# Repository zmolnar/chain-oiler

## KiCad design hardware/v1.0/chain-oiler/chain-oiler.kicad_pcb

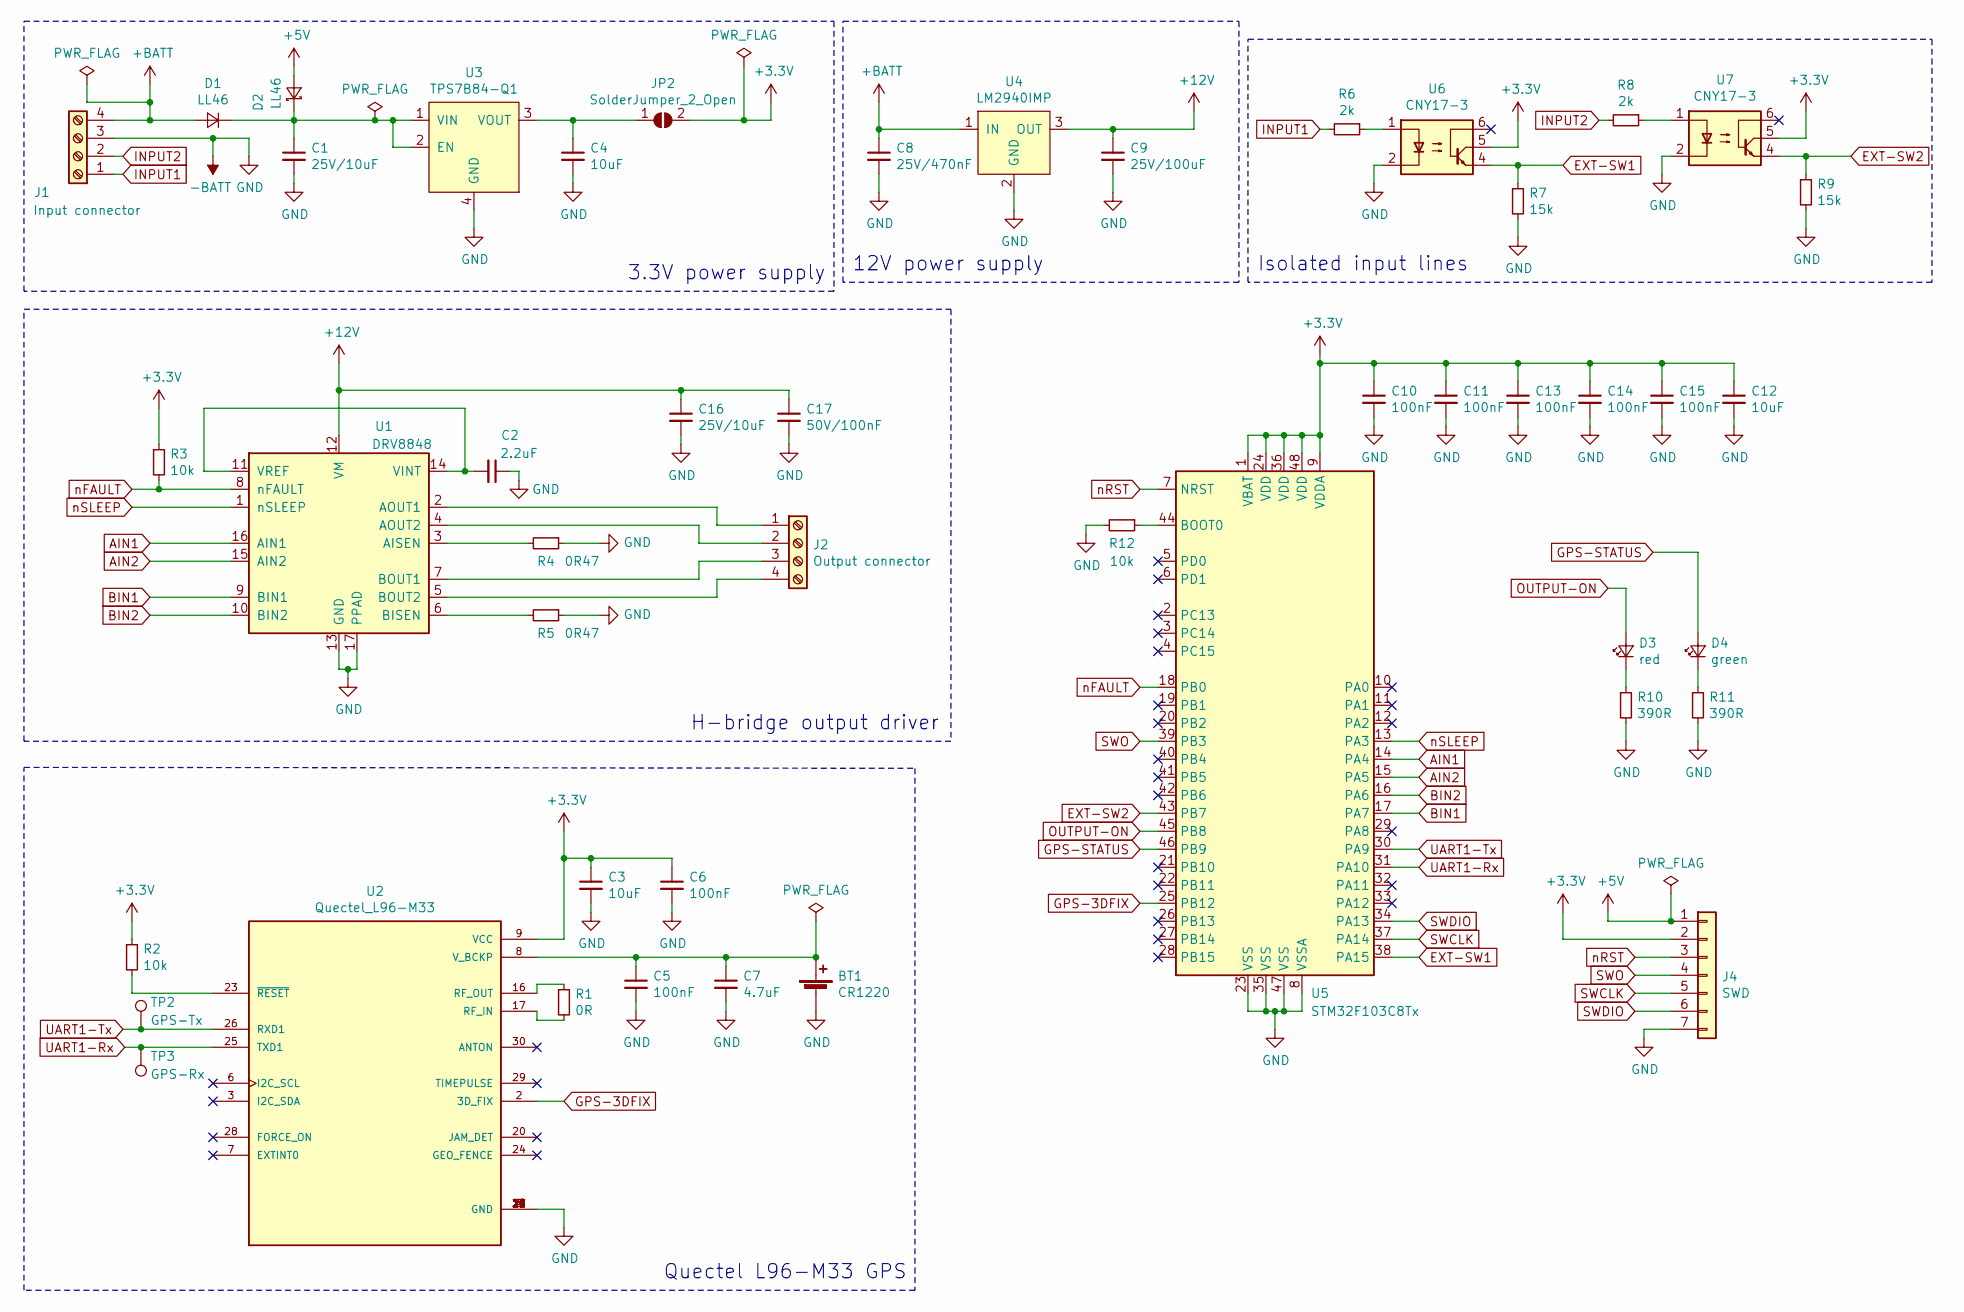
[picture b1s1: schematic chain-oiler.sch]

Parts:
BT1: CR1220; BatteryHolder_Keystone_3001_1x12mm
C1, C16: 25V/10uF; C_0805_2012Metric_Pad1.15x1.40mm_HandSolder
C2: 2.2uF; C_0805_2012Metric_Pad1.15x1.40mm_HandSolder
C3, C4, C12: 10uF; C_0603_1608Metric_Pad1.05x0.95mm_HandSolder
C5, C6, C10, C11, C13, C14, C15: 100nF; C_0603_1608Metric_Pad1.05x0.95mm_HandSolder
C7: 4.7uF; C_0603_1608Metric_Pad1.05x0.95mm_HandSolder
C8: 25V/470nF; C_0603_1608Metric_Pad1.05x0.95mm_HandSolder
C9: 25V/100uF; CP_Radial_D6.3mm_P2.50mm
C17: 50V/100nF; C_0603_1608Metric_Pad1.05x0.95mm_HandSolder
D1, D2: LL46; D_MiniMELF
D3: red; D_0603_1608Metric_Pad1.05x0.95mm_HandSolder
D4: green; D_0603_1608Metric_Pad1.05x0.95mm_HandSolder
J1: Input connector; Tianli_TLPHC100R_3.81_01x04
J2: Output connector; Tianli_TLPHC100R_3.81_01x04
J4: SWD; PinHeader_1x07_P2.54mm_Vertical
JP2: SolderJumper_2_Open; SolderJumper-2_P1.3mm_Open_TrianglePad1.0x1.5mm
R1: 0R; R_0603_1608Metric_Pad1.05x0.95mm_HandSolder
R2, R3, R12: 10k; R_0603_1608Metric_Pad1.05x0.95mm_HandSolder
R4, R5: 0R47; R_0805_2012Metric_Pad1.15x1.40mm_HandSolder
R6, R8: 2k; R_0603_1608Metric_Pad1.05x0.95mm_HandSolder
R7, R9: 15k; R_0805_2012Metric_Pad1.15x1.40mm_HandSolder
R10, R11: 390R; R_0603_1608Metric_Pad1.05x0.95mm_HandSolder
TP2: GPS-Tx; TestPoint_Pad_D1.0mm
TP3: GPS-Rx; TestPoint_Pad_D1.0mm
U1: DRV8848; TSSOP-16-1EP_4.4x5mm_P0.65mm
U2: Quectel_L96-M33
U3: TPS7B84-Q1; SOT-223
U4: LM2940IMP; SOT-223-3_TabPin2
U5: STM32F103C8Tx; LQFP-48_7x7mm_P0.5mm
U6, U7: CNY17-3; SMDIP-6_W9.53mm

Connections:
+3V3: C3.1, C6.1, C10.1, C11.1, C12.1, C13.1, C14.1, C15.1, J4.2, JP2.2 (B), R2.1, R3.1, U2.9 (VCC), U5.1 (VBAT), U5.9 (VDDA), U5.24 (VDD), U5.36 (VDD), U5.48 (VDD), U6.5, U7.5
+5V: D2.2 (A), J4.1
+12V: C9.1, C16.1, C17.1, U1.12 (VM), U4.3 (OUT)
+BATT: C8.1, D1.2 (A), J1.4, U4.1 (IN)
-BATT: BT1.2 (-), C1.2, C2.1, C3.2, C4.2, C5.2, C6.2, C7.2, C8.2, C9.2, C10.2, C11.2, C12.2, C13.2, C14.2, C15.2, C16.2, C17.2, J1.3, J4.7, R4.1, R5.1, R7.2, R9.2, R10.2, R11.2, R12.2, U1.13 (GND), U1.17 (PPAD), U2.4 (GND), U2.5 (GND), U2.10 (GND), U2.11 (GND), U2.12 (GND), U2.13 (GND), U2.14 (GND), U2.15 (GND), U2.18 (GND), U2.19 (GND), U2.21 (GND), U2.22 (GND), U2.27 (GND), U2.31 (GND), U3.4 (GND), U4.2 (GND), U5.8 (VSSA), U5.23 (VSS), U5.35 (VSS), U5.47 (VSS), U6.2, U7.2
AIN1: U1.16 (AIN1), U5.14 (PA4)
AIN2: U1.15 (AIN2), U5.15 (PA5)
BIN1: U1.9 (BIN1), U5.17 (PA7)
BIN2: U1.10 (BIN2), U5.16 (PA6)
EXT-SW1: R7.1, U5.38 (PA15), U6.4
EXT-SW2: R9.1, U5.43 (PB7), U7.4
GPS-3DFIX: U2.2 (3D_FIX), U5.25 (PB12)
GPS-STATUS: D4.2 (A), U5.46 (PB9)
INPUT1: J1.1, R6.2
INPUT2: J1.2, R8.2
unnamed: BT1.1 (+), C5.1, C7.1, U2.8 (V_BCKP)
unnamed: C1.1, D1.1 (K), D2.1 (K), U3.1 (VIN), U3.2 (EN)
unnamed: C2.2, U1.11 (VREF), U1.14 (VINT)
unnamed: C4.1, JP2.1 (A), U3.3 (VOUT)
unnamed: D3.1 (K), R10.1
unnamed: D4.1 (K), R11.1
unnamed: J2.1, U1.2 (AOUT1)
unnamed: J2.2, U1.4 (AOUT2)
unnamed: J2.3, U1.7 (BOUT1)
unnamed: J2.4, U1.5 (BOUT2)
unnamed: R1.1, U2.16 (RF_OUT)
unnamed: R1.2, U2.17 (RF_IN)
unnamed: R2.2, U2.23 (~RESET)
unnamed: R4.2, U1.3 (AISEN)
unnamed: R5.2, U1.6 (BISEN)
unnamed: R6.1, U6.1
unnamed: R8.1, U7.1
unnamed: R12.1, U5.44 (BOOT0)
OUTPUT-ON: D3.2 (A), U5.45 (PB8)
SWCLK: J4.5, U5.37 (PA14)
SWDIO: J4.6, U5.34 (PA13)
SWO: J4.4, U5.39 (PB3)
UART1-Rx: TP3.1, U2.25 (TXD1), U5.31 (PA10)
UART1-Tx: TP2.1, U2.26 (RXD1), U5.30 (PA9)
nFAULT: R3.2, U1.8 (nFAULT), U5.18 (PB0)
nRST: J4.3, U5.7 (NRST)
nSLEEP: U1.1 (nSLEEP), U5.13 (PA3)

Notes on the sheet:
3.3V power supply
12V power supply
H-bridge output driver
Isolated input lines
Quectel L96-M33 GPS

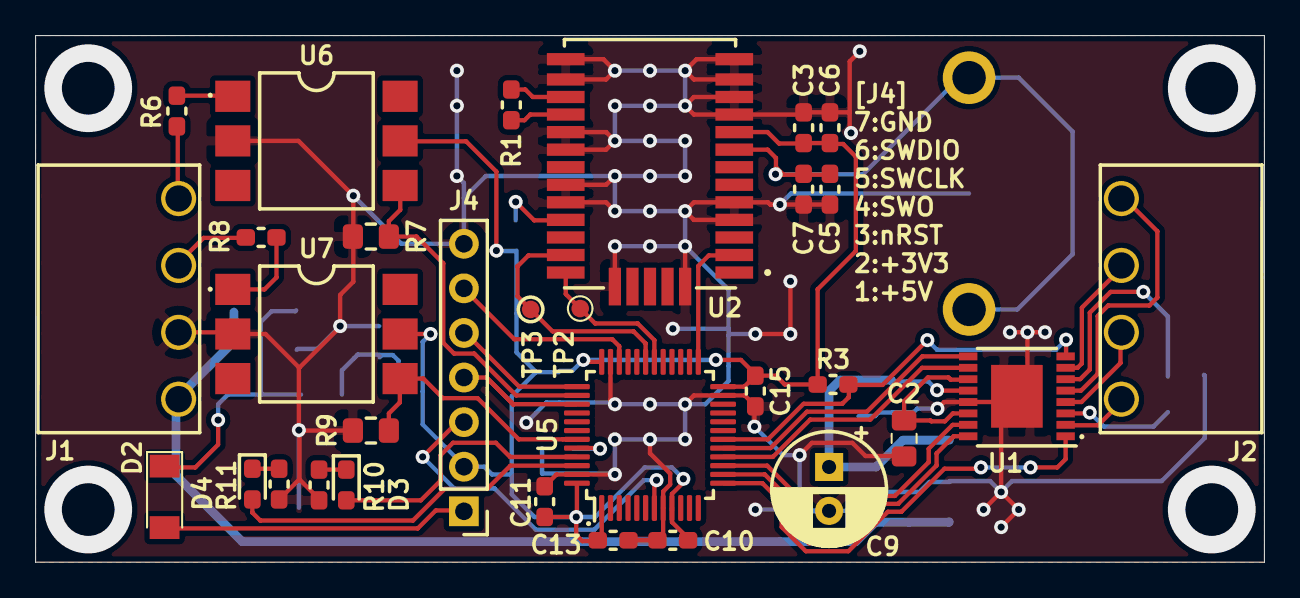
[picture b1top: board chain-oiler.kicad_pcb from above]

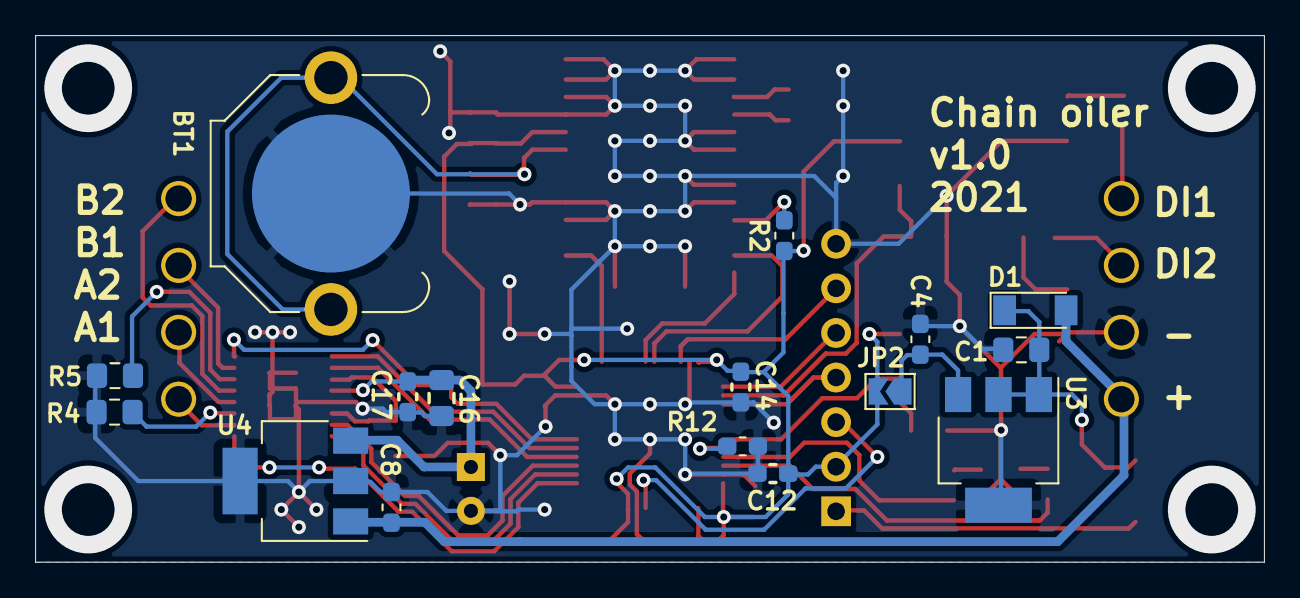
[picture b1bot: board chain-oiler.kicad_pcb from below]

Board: 2 copper layers, 70.0 x 30.0 mm, 47 parts (16 on the bottom side), 42 nets.

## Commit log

2021-07-03 Add v1.0 board project
2021-07-03 Initialize zephyr project
2021-07-20 Add v1.0 hardware design files.
2021-07-20 Add ChibiOS submodule
2021-07-21 Create blinky app
2021-07-21 Add VSCode cortex debug config
2021-07-21 Add GPS reader thread
2021-07-21 Configure USART1 for Quectel GPS
2021-07-22 Implement GPS management
2021-07-25 Implement chain oiler DC motor handling
